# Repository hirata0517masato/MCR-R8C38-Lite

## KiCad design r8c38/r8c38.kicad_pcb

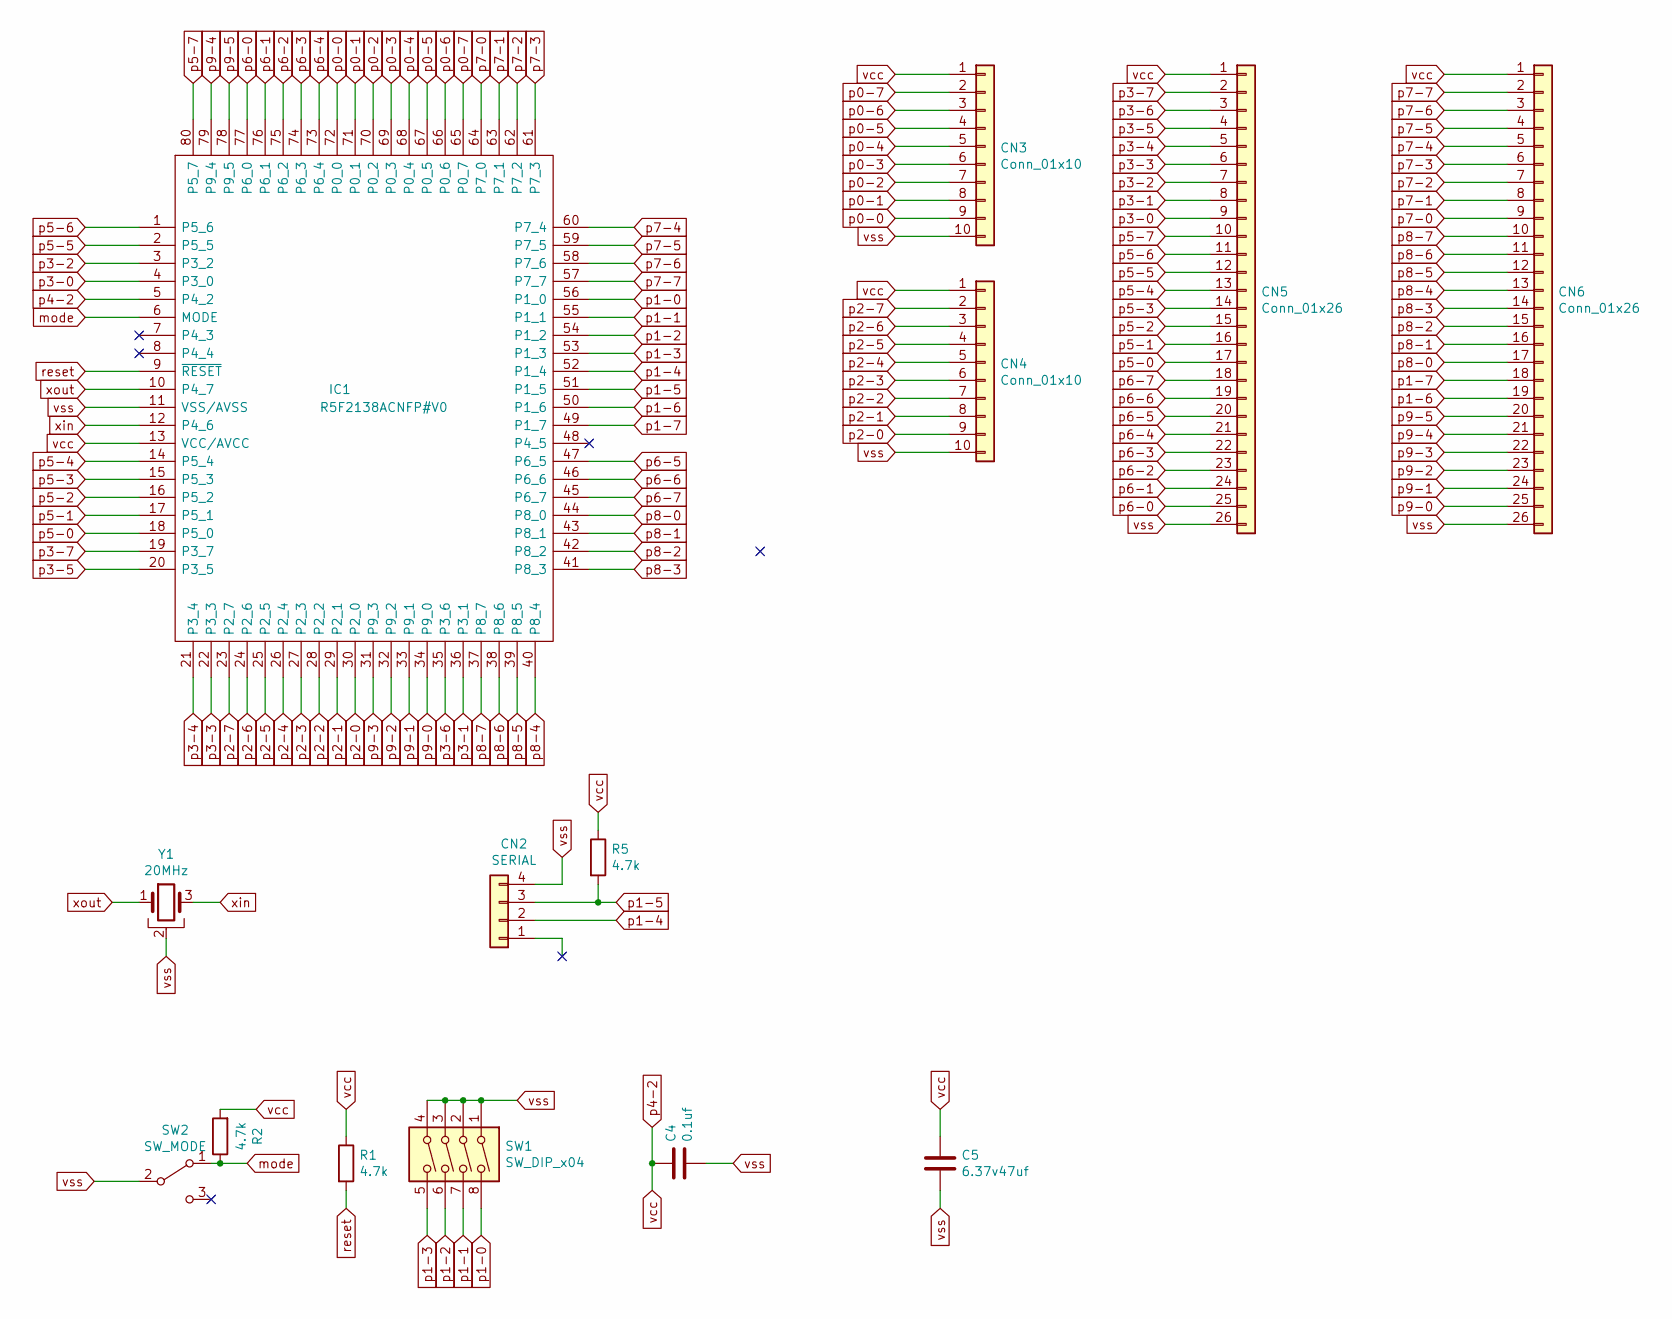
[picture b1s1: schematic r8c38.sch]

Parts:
C4: 0.1uf; CP_EIA-1608-10_AVX-L
C5: 6.37v47uf; CP_Elec_5x5.8
CN2: SERIAL; PinHeader_1x04_P2.54mm_Vertical
CN3, CN4: Conn_01x10; PinHeader_2x05_P2.54mm_Vertical
CN5, CN6: Conn_01x26; PinHeader_2x13_P2.54mm_Vertical
IC1: R5F2138ACNFP#V0; QFP50P1400X1400X170-80N; Manufacturer_Part_Number R5F2138ACNFP#V0
R1, R2, R5: 4.7k; CP_EIA-1608-10_AVX-L
SW1: SW_DIP_x04; SW_DIP_SPSTx04_Slide_9.78x12.34mm_W7.62mm_P2.54mm
SW2: SW_MODE; PinHeader_1x03_P2.54mm_Vertical
Y1: 20MHz; Resonator_SMD_muRata_CSTxExxV-3Pin_3.0x1.1mm_HandSoldering

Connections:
mode: IC1.6 (MODE), R2.1, SW2.1 (A)
p0-0: CN3.9, IC1.72 (P0_0)
p0-1: CN3.8, IC1.71 (P0_1)
p0-2: CN3.7, IC1.70 (P0_2)
p0-3: CN3.6, IC1.69 (P0_3)
p0-4: CN3.5, IC1.68 (P0_4)
p0-5: CN3.4, IC1.67 (P0_5)
p0-6: CN3.3, IC1.66 (P0_6)
p0-7: CN3.2, IC1.65 (P0_7)
p1-0: IC1.56 (P1_0), SW1.8
p1-1: IC1.55 (P1_1), SW1.7
p1-2: IC1.54 (P1_2), SW1.6
p1-3: IC1.53 (P1_3), SW1.5
p1-4: CN2.2, IC1.52 (P1_4)
p1-5: CN2.3, IC1.51 (P1_5), R5.2
p1-6: CN6.19, IC1.50 (P1_6)
p1-7: CN6.18, IC1.49 (P1_7)
p2-0: CN4.9, IC1.30 (P2_0)
p2-1: CN4.8, IC1.29 (P2_1)
p2-2: CN4.7, IC1.28 (P2_2)
p2-3: CN4.6, IC1.27 (P2_3)
p2-4: CN4.5, IC1.26 (P2_4)
p2-5: CN4.4, IC1.25 (P2_5)
p2-6: CN4.3, IC1.24 (P2_6)
p2-7: CN4.2, IC1.23 (P2_7)
p3-0: CN5.9, IC1.4 (P3_0)
p3-1: CN5.8, IC1.36 (P3_1)
p3-2: CN5.7, IC1.3 (P3_2)
p3-3: CN5.6, IC1.22 (P3_3)
p3-4: CN5.5, IC1.21 (P3_4)
p3-5: CN5.4, IC1.20 (P3_5)
p3-6: CN5.3, IC1.35 (P3_6)
p3-7: CN5.2, IC1.19 (P3_7)
p4-2: C4.1, C5.1, CN3.1, CN4.1, CN5.1, CN6.1, IC1.5 (P4_2), IC1.13 (VCC/AVCC), R1.1, R2.2, R5.1
p5-0: CN5.17, IC1.18 (P5_0)
p5-1: CN5.16, IC1.17 (P5_1)
p5-2: CN5.15, IC1.16 (P5_2)
p5-3: CN5.14, IC1.15 (P5_3)
p5-4: CN5.13, IC1.14 (P5_4)
p5-5: CN5.12, IC1.2 (P5_5)
p5-6: CN5.11, IC1.1 (P5_6)
p5-7: CN5.10, IC1.80 (P5_7)
p6-0: CN5.25, IC1.77 (P6_0)
p6-1: CN5.24, IC1.76 (P6_1)
p6-2: CN5.23, IC1.75 (P6_2)
p6-3: CN5.22, IC1.74 (P6_3)
p6-4: CN5.21, IC1.73 (P6_4)
p6-5: CN5.20, IC1.47 (P6_5)
p6-6: CN5.19, IC1.46 (P6_6)
p6-7: CN5.18, IC1.45 (P6_7)
p7-0: CN6.9, IC1.64 (P7_0)
p7-1: CN6.8, IC1.63 (P7_1)
p7-2: CN6.7, IC1.62 (P7_2)
p7-3: CN6.6, IC1.61 (P7_3)
p7-4: CN6.5, IC1.60 (P7_4)
p7-5: CN6.4, IC1.59 (P7_5)
p7-6: CN6.3, IC1.58 (P7_6)
p7-7: CN6.2, IC1.57 (P7_7)
p8-0: CN6.17, IC1.44 (P8_0)
p8-1: CN6.16, IC1.43 (P8_1)
p8-2: CN6.15, IC1.42 (P8_2)
p8-3: CN6.14, IC1.41 (P8_3)
p8-4: CN6.13, IC1.40 (P8_4)
p8-5: CN6.12, IC1.39 (P8_5)
p8-6: CN6.11, IC1.38 (P8_6)
p8-7: CN6.10, IC1.37 (P8_7)
p9-0: CN6.25, IC1.34 (P9_0)
p9-1: CN6.24, IC1.33 (P9_1)
p9-2: CN6.23, IC1.32 (P9_2)
p9-3: CN6.22, IC1.31 (P9_3)
p9-4: CN6.21, IC1.79 (P9_4)
p9-5: CN6.20, IC1.78 (P9_5)
reset: IC1.9 (~RESET), R1.2
vss: C4.2, C5.2, CN2.4, CN3.10, CN4.10, CN5.26, CN6.26, IC1.11 (VSS/AVSS), SW1.1, SW1.2, SW1.3, SW1.4, SW2.2 (B), Y1.2
xin: IC1.12 (P4_6), Y1.3
xout: IC1.10 (P4_7), Y1.1

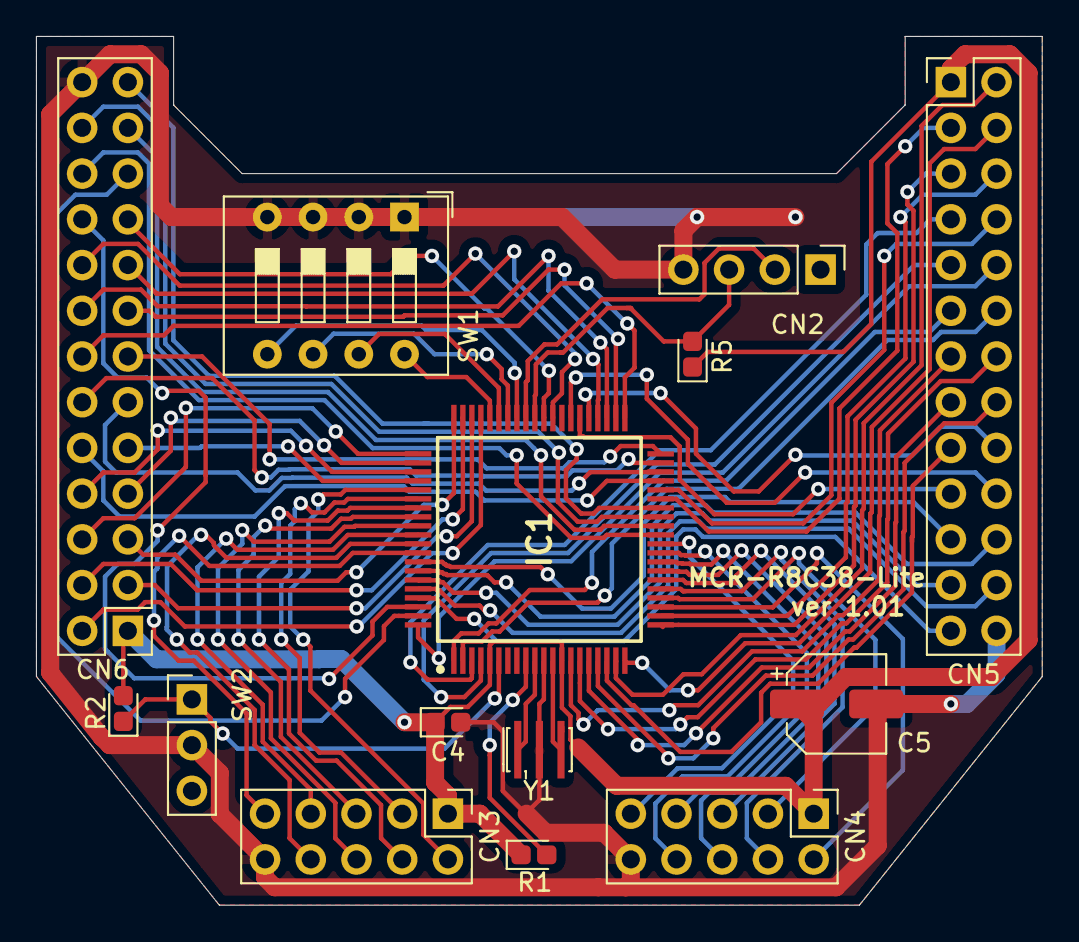
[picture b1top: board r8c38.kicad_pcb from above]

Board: 2 copper layers, 55.9 x 48.3 mm, 14 parts (0 on the bottom side), 76 nets.

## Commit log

2020-08-29 add
    add
2020-08-29 v1.01
    v1.01
